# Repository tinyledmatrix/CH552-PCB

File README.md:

# CH552-PCB
CH552 Test-PCB

TODO add more info/images

Documentation licensed under the Creative Commons Attribution Share Alike 4.0 International License
Hardware licend under the CERN Open Hardware Licence v1.2

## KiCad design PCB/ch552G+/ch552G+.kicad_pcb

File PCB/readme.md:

untested Kicad Files use on your own risk

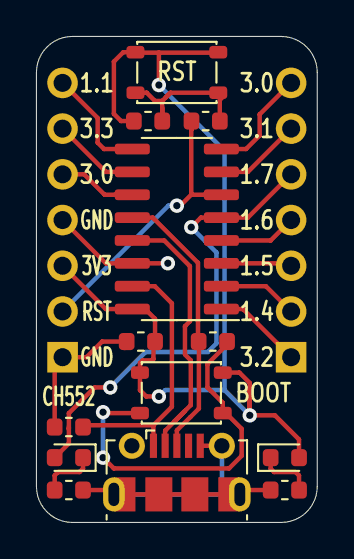
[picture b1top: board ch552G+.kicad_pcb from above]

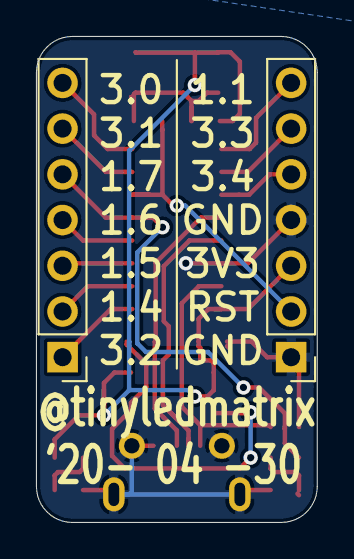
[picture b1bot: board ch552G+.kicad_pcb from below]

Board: 2 copper layers, 15.6 x 27.0 mm, 15 parts (2 on the bottom side), 20 nets.

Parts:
C1: C; C_0603_1608Metric
C2, C3: 1u; C_0603_1608Metric
D1, D2: LED; LED_0603_1608Metric
IC1: CH552G; SOIC-16_3.9x9.9mm_P1.27mm
J1, J3: Conn_01x07; PinHeader_1x07_P2.54mm_Vertical
J2: USB_B_Micro; USB_Micro-B_Molex-105017-0001
R1, R2, R3, R4: 1k; R_0603_1608Metric
SW1, SW2: SW_Push; SW_SPST_3x4x2.5

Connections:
+3V3: C1.1, C3.1, D1.2, IC1.16, J3.3, SW1.1, SW2.1
/P1.1: IC1.9, J3.7
/P1.4: IC1.2, J1.2
/P1.5: IC1.3, J1.3
/P1.6: IC1.4, J1.4
/P1.7: D2.2, IC1.5, J1.5
/P3.0: IC1.8, J1.7
/P3.1: IC1.7, J1.6
/P3.2: IC1.1, J1.1
/P3.3: IC1.10, J3.6
/P3.4: IC1.11, J3.5
/RST: IC1.6, J3.2, R1.1
GND: C2.2, C3.2, IC1.14, J2.5, J2.6, J3.1, J3.4, R3.1, R4.1
unnamed: C1.2, R1.2, SW2.2
unnamed: D1.1, R3.2
unnamed: D2.1, R4.2
unnamed: IC1.12, J2.3, R2.1
unnamed: IC1.13, J2.2
unnamed: R2.2, SW1.2
VBUS: C2.1, IC1.15, J2.1

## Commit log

2020-05-09 initial commit to git
    Push all the stuff to git
2020-05-09 Minor fixes
